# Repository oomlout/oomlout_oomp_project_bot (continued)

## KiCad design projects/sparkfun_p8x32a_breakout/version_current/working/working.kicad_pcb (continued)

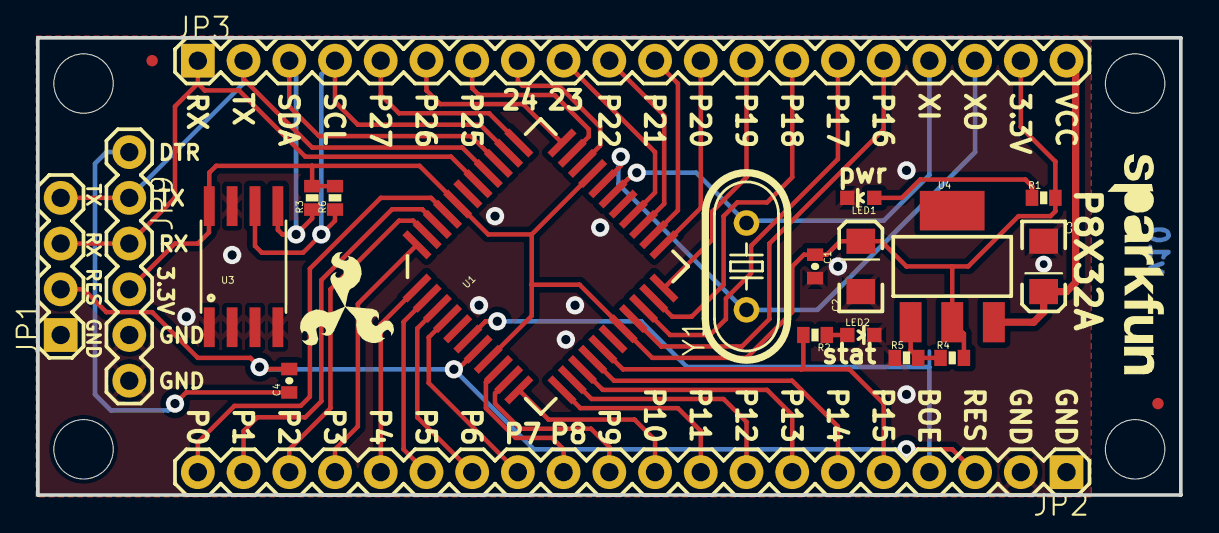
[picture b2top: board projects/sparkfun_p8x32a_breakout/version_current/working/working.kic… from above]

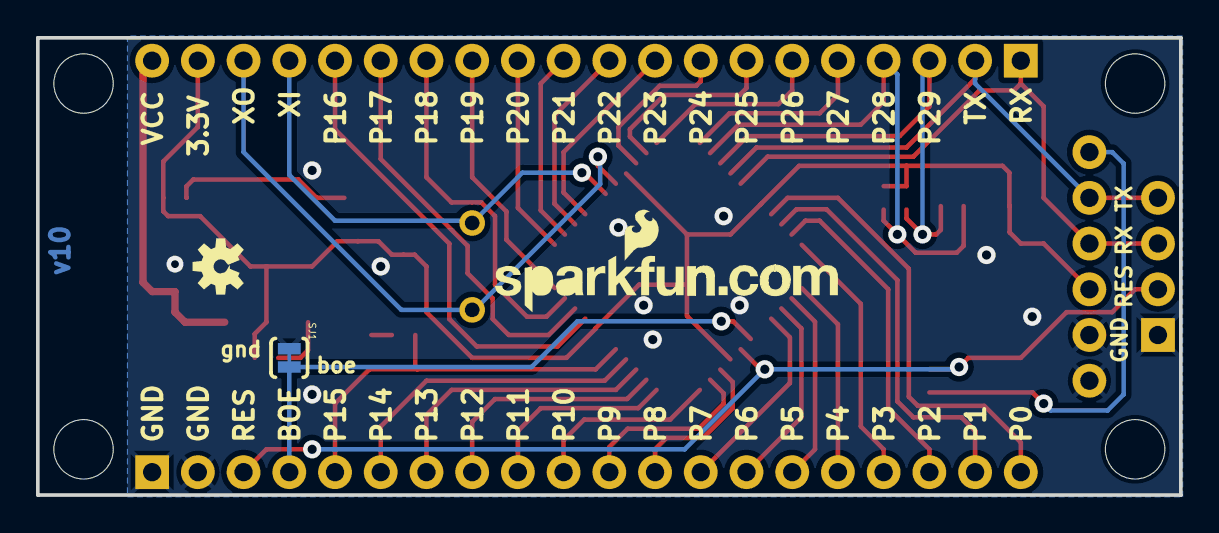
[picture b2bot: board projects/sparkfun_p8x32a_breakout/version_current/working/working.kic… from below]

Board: 2 copper layers, 63.5 x 25.4 mm, 34 parts (3 on the bottom side), 43 nets.

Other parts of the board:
JP6, JP8: LOGO-SFESK; SFE-LOGO-FLAME

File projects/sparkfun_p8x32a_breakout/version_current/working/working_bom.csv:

"Id";"Designator";"Footprint";"Quantity";"Designation";"Supplier and ref";
1;"JP13,JP12,JP10,JP11";"STAND-OFF";4;"STAND-OFF";;;
2;"JP8,JP6,JP7";"SFE-LOGO-FLAME";3;"LOGO-SFESK";;;
3;"JP9";"FTDI_BASIC";1;"FTDI_BASICPTH";;;
4;"JP3,JP2";"1X20";2;"M20";;;
5;"JP1";"1X04";1;"PropPlug";;;
6;"R6,R3";"0402-RES";2;"10k";;;
7;"U3";"SO08-EIAJ";1;"EEPROM-I2CEIAJ";;;
8;"C4,C1";"0402-CAP";2;"0.1uF";;;
9;"JP14";"SFE-NEW-WEB";1;"LOGO-SFENW2";;;
10;"FRAME1";"CREATIVE_COMMONS";1;"FRAME-LETTER";;;
11;"R1,R2";"0402-RES";2;"330";;;
12;"JP4,JP15";"MICRO-FIDUCIAL";2;"FIDUCIALUFIDUCIAL";;;
13;"C2,C3";"EIA3216";2;"10uF";;;
14;"R5";"0402-RES";1;"390";;;
15;"U1";"P8X32A-Q44";1;"";;;
16;"LED1";"LED-0603";1;"red";;;
17;"LED2";"LED-0603";1;"yellow";;;
18;"R4";"0402-RES";1;"240";;;
19;"U4";"SOT223";1;"V_REG_317SMD";;;
20;"Y1";"HC49U-V";1;"";;;
21;"SJ1";"SJ_2S-TRACE";1;"SOLDERJUMPERTRACE";;;
22;"U$1";"OSHW-LOGO-S";1;"OSHW-LOGOS";;;
23;"JP5";"SFE-NEW-WEBLOGO";1;"LOGO-SFENEW";;;

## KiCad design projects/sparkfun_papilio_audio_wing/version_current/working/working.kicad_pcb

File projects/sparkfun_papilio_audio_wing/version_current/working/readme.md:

# Papilio_Audio_Wing by sparkfun  
This is a harvested standardized copy of a project from github.  
The original project can be found at:  
https://github.com/sparkfun/Papilio_Audio_Wing  
Please consult that link for additional, details, files, and license information.  
Note: It was auto harvested and if the original repo had more than one board file or anything out of the ordinary the files here are likely not representative.

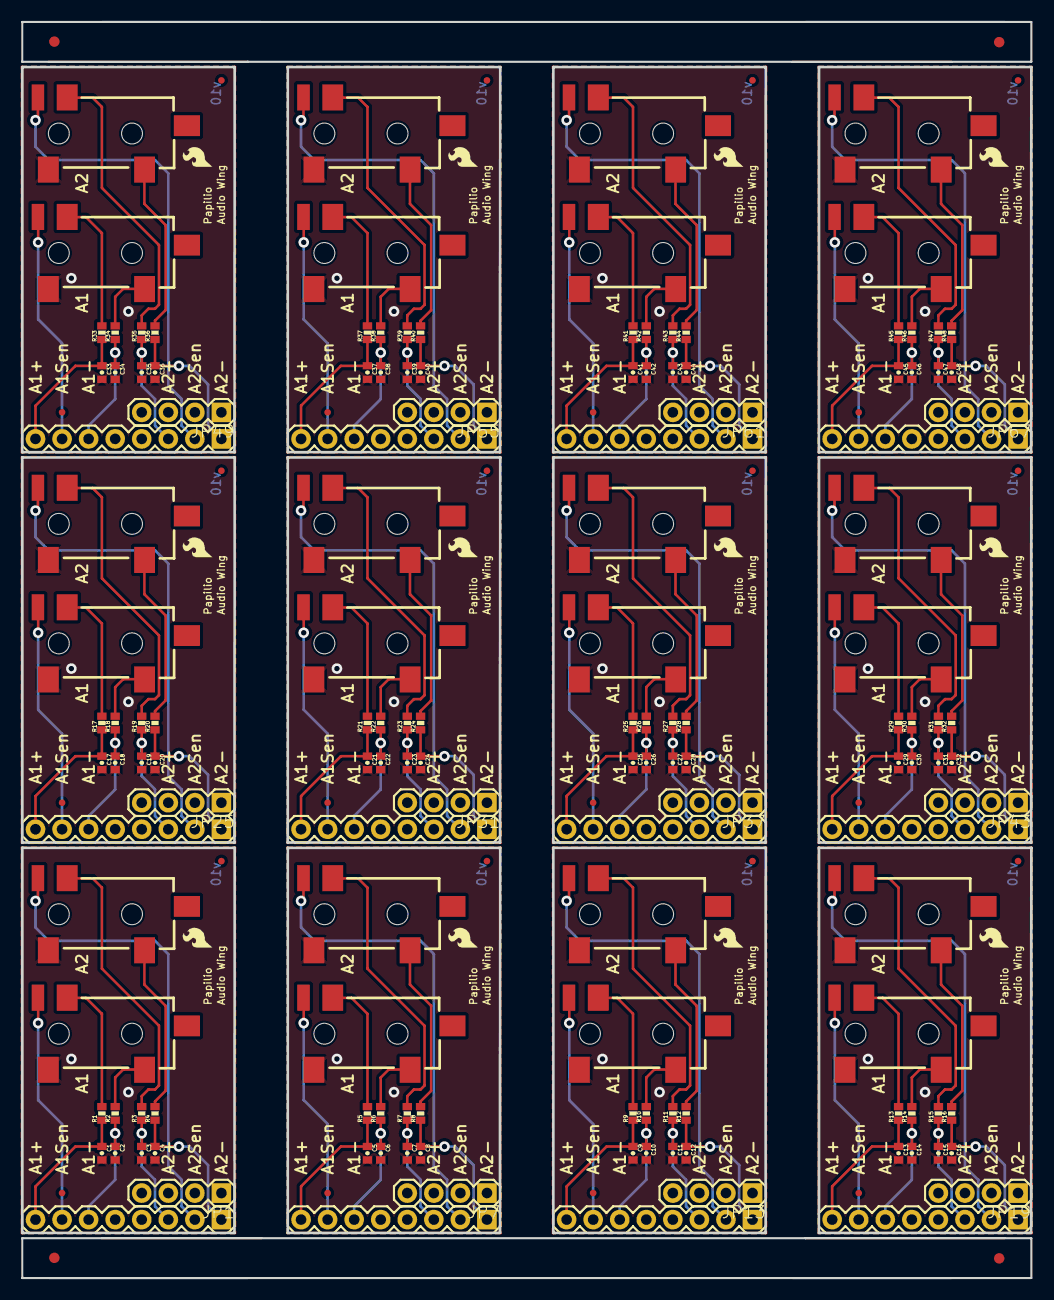
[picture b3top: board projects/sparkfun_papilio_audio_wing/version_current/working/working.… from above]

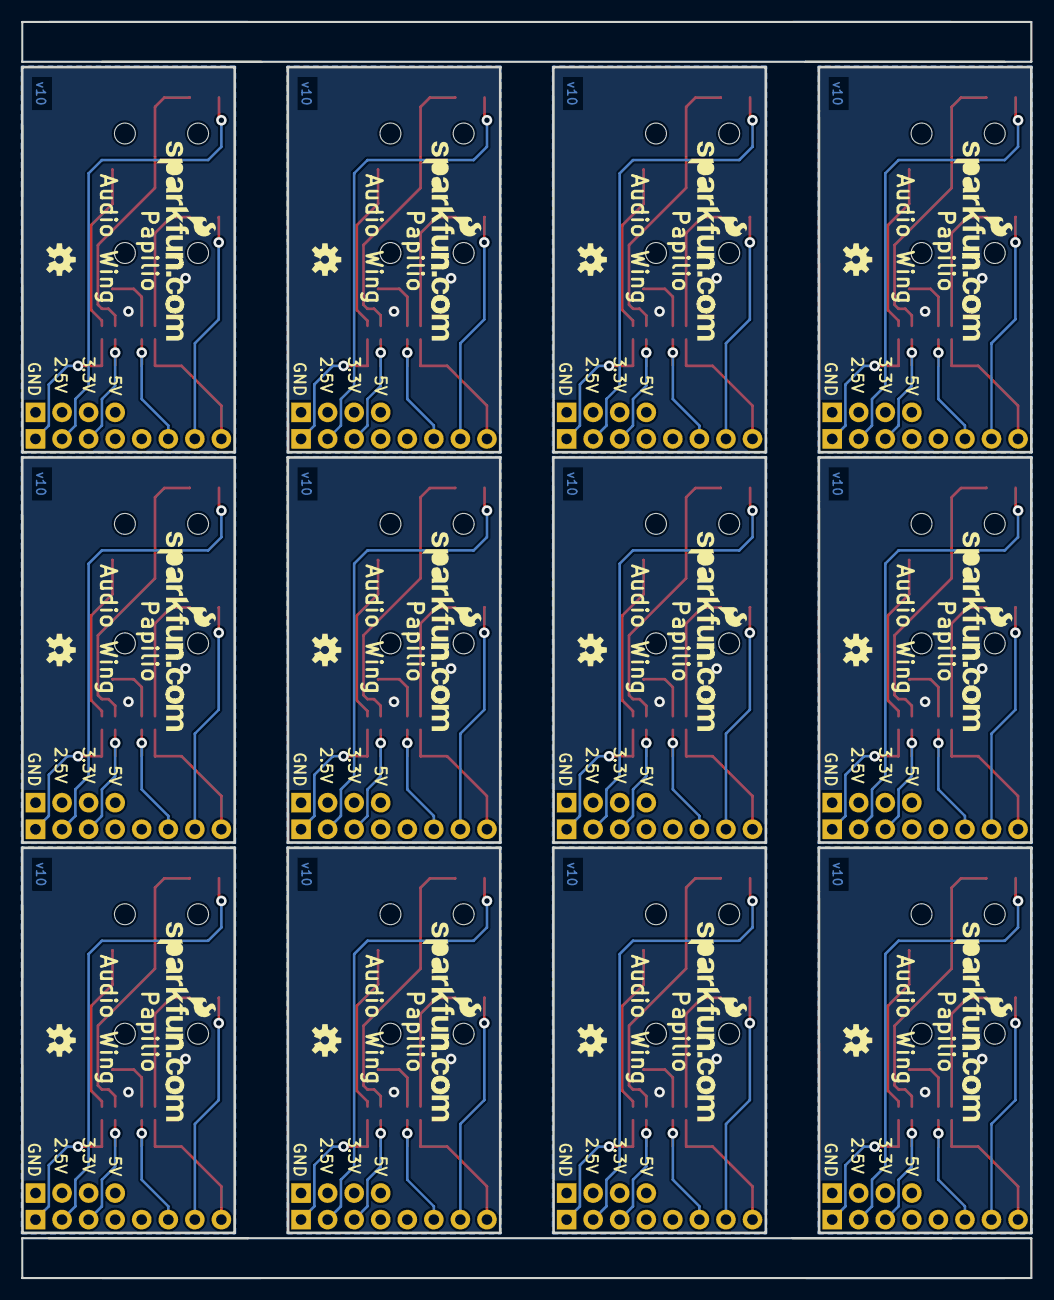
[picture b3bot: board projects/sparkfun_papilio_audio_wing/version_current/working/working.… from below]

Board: 2 copper layers, 96.5 x 120.1 mm, 208 parts (24 on the bottom side), 132 nets.

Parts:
AJ1, AJ2, AJ3, AJ4, AJ5, AJ6, AJ7, AJ8, AJ9, AJ10, AJ11, AJ12, AJ13, AJ14, AJ15, AJ16, AJ17, AJ18, AJ19, AJ20, AJ21, AJ22, AJ23, AJ24: AUDIO-JACK2SMD; AUDIO-JACK-3.5MM-SMD
C1, C2, C3, C4, C5, C6, C7, C8, C9, C10, C11, C12, C13, C14, C15, C16, C17, C18, C19, C20, C21, C22, C23, C24, C25, C26, C27, C28, C29, C30, C31, C32, C33, C34, C35, C36, C37, C38, C39, C40, C41, C42, C43, C44, C45, C46, C47, C48: 4.7nF; 0402-CAP
E$1, E$2, E$3, E$4: FIDUCIAL-1X2
JP1, JP7, JP13, JP19, JP25, JP31, JP37, JP43, JP49, JP55, JP61, JP67: 1X04
JP2, JP8, JP14, JP20, JP26, JP32, JP38, JP44, JP50, JP56, JP62, JP68: 1X08
JP3, JP9, JP15, JP21, JP27, JP33, JP39, JP45, JP51, JP57, JP63, JP69: LOGO-SFESK; SFE-LOGO-FLAME
JP4, JP10, JP16, JP22, JP28, JP34, JP40, JP46, JP52, JP58, JP64, JP70: LOGO-SFENEW; SFE-NEW-WEBLOGO
JP5, JP6, JP11, JP12, JP17, JP18, JP23, JP24, JP29, JP30, JP35, JP36, JP41, JP42, JP47, JP48, JP53, JP54, JP59, JP60, JP65, JP66, JP71, JP72: FIDUCIALUFIDUCIAL; MICRO-FIDUCIAL
R1, R2, R3, R4, R5, R6, R7, R8, R9, R10, R11, R12, R13, R14, R15, R16, R17, R18, R19, R20, R21, R22, R23, R24, R25, R26, R27, R28, R29, R30, R31, R32, R33, R34, R35, R36, R37, R38, R39, R40, R41, R42, R43, R44, R45, R46, R47, R48: 3.3k; 0402-RES
U$1, U$2, U$3, U$4, U$5, U$6, U$7, U$8, U$9, U$10, U$11, U$12: OSHW-LOGOS; OSHW-LOGO-S

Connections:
A1+: C1.1, JP2.8, R1.1
A1+1: C5.1, JP8.8, R5.1
A1+2: C9.1, JP14.8, R9.1
A1+3: C13.1, JP20.8, R13.1
A1+4: C17.1, JP26.8, R17.1
A1+5: C21.1, JP32.8, R21.1
A1+6: C25.1, JP38.8, R25.1
A1+7: C29.1, JP44.8, R29.1
A1+8: C33.1, JP50.8, R33.1
A1+9: C37.1, JP56.8, R37.1
A1+10: C41.1, JP62.8, R41.1
A1+11: C45.1, JP68.8, R45.1
A1-: C2.1, JP2.6, R2.1
A1-1: C6.1, JP8.6, R6.1
A1-2: C10.1, JP14.6, R10.1
A1-3: C14.1, JP20.6, R14.1
A1-4: C18.1, JP26.6, R18.1
A1-5: C22.1, JP32.6, R22.1
A1-6: C26.1, JP38.6, R26.1
A1-7: C30.1, JP44.6, R30.1
A1-8: C34.1, JP50.6, R34.1
A1-9: C38.1, JP56.6, R38.1
A1-10: C42.1, JP62.6, R42.1
A1-11: C46.1, JP68.6, R46.1
A1SEN: AJ1.RSH, JP2.7
A1SEN1: AJ3.RSH, JP8.7
A1SEN2: AJ5.RSH, JP14.7
A1SEN3: AJ7.RSH, JP20.7
A1SEN4: AJ9.RSH, JP26.7
A1SEN5: AJ11.RSH, JP32.7
A1SEN6: AJ13.RSH, JP38.7
A1SEN7: AJ15.RSH, JP44.7
A1SEN8: AJ17.RSH, JP50.7
A1SEN9: AJ19.RSH, JP56.7
A1SEN10: AJ21.RSH, JP62.7
A1SEN11: AJ23.RSH, JP68.7
A2+: C3.1, JP2.3, R3.1
A2+1: C7.1, JP8.3, R7.1
A2+2: C11.1, JP14.3, R11.1
A2+3: C15.1, JP20.3, R15.1
A2+4: C19.1, JP26.3, R19.1
A2+5: C23.1, JP32.3, R23.1
A2+6: C27.1, JP38.3, R27.1
A2+7: C31.1, JP44.3, R31.1
A2+8: C35.1, JP50.3, R35.1
A2+9: C39.1, JP56.3, R39.1
A2+10: C43.1, JP62.3, R43.1
A2+11: C47.1, JP68.3, R47.1
A2-: C4.1, JP2.1, R4.1
A2-1: C8.1, JP8.1, R8.1
A2-2: C12.1, JP14.1, R12.1
A2-3: C16.1, JP20.1, R16.1
A2-4: C20.1, JP26.1, R20.1
A2-5: C24.1, JP32.1, R24.1
A2-6: C28.1, JP38.1, R28.1
A2-7: C32.1, JP44.1, R32.1
A2-8: C36.1, JP50.1, R36.1
A2-9: C40.1, JP56.1, R40.1
A2-10: C44.1, JP62.1, R44.1
A2-11: C48.1, JP68.1, R48.1
A2SEN: AJ2.RSH, JP2.2
A2SEN1: AJ4.RSH, JP8.2
A2SEN2: AJ6.RSH, JP14.2
A2SEN3: AJ8.RSH, JP20.2
A2SEN4: AJ10.RSH, JP26.2
A2SEN5: AJ12.RSH, JP32.2
A2SEN6: AJ14.RSH, JP38.2
A2SEN7: AJ16.RSH, JP44.2
A2SEN8: AJ18.RSH, JP50.2
A2SEN9: AJ20.RSH, JP56.2
A2SEN10: AJ22.RSH, JP62.2
A2SEN11: AJ24.RSH, JP68.2
GND: AJ1.SLEEVE, AJ2.SLEEVE, C1.2, C2.2, C3.2, C4.2, JP1.1
GND1: AJ3.SLEEVE, AJ4.SLEEVE, C5.2, C6.2, C7.2, C8.2, JP7.1
GND2: AJ5.SLEEVE, AJ6.SLEEVE, C9.2, C10.2, C11.2, C12.2, JP13.1
GND3: AJ7.SLEEVE, AJ8.SLEEVE, C13.2, C14.2, C15.2, C16.2, JP19.1
GND4: AJ9.SLEEVE, AJ10.SLEEVE, C17.2, C18.2, C19.2, C20.2, JP25.1
GND5: AJ11.SLEEVE, AJ12.SLEEVE, C21.2, C22.2, C23.2, C24.2, JP31.1
GND6: AJ13.SLEEVE, AJ14.SLEEVE, C25.2, C26.2, C27.2, C28.2, JP37.1
GND7: AJ15.SLEEVE, AJ16.SLEEVE, C29.2, C30.2, C31.2, C32.2, JP43.1
GND8: AJ17.SLEEVE, AJ18.SLEEVE, C33.2, C34.2, C35.2, C36.2, JP49.1
GND9: AJ19.SLEEVE, AJ20.SLEEVE, C37.2, C38.2, C39.2, C40.2, JP55.1
GND10: AJ21.SLEEVE, AJ22.SLEEVE, C41.2, C42.2, C43.2, C44.2, JP61.1
GND11: AJ23.SLEEVE, AJ24.SLEEVE, C45.2, C46.2, C47.2, C48.2, JP67.1
unnamed: AJ2.RING, R3.2
unnamed: AJ2.TIP, R4.2
unnamed: AJ1.RING, R1.2
unnamed: AJ1.TIP, R2.2
unnamed: AJ4.RING, R7.2
unnamed: AJ4.TIP, R8.2
unnamed: AJ3.RING, R5.2
unnamed: AJ3.TIP, R6.2
unnamed: AJ6.RING, R11.2
unnamed: AJ6.TIP, R12.2
unnamed: AJ5.RING, R9.2
unnamed: AJ5.TIP, R10.2
unnamed: AJ8.RING, R15.2
unnamed: AJ8.TIP, R16.2
unnamed: AJ7.RING, R13.2
unnamed: AJ7.TIP, R14.2
unnamed: AJ10.RING, R19.2
unnamed: AJ10.TIP, R20.2
unnamed: AJ9.RING, R17.2
unnamed: AJ9.TIP, R18.2
unnamed: AJ12.RING, R23.2
unnamed: AJ12.TIP, R24.2
unnamed: AJ11.RING, R21.2
unnamed: AJ11.TIP, R22.2
unnamed: AJ14.RING, R27.2
unnamed: AJ14.TIP, R28.2
unnamed: AJ13.RING, R25.2
unnamed: AJ13.TIP, R26.2
unnamed: AJ16.RING, R31.2
unnamed: AJ16.TIP, R32.2
unnamed: AJ15.RING, R29.2
unnamed: AJ15.TIP, R30.2
unnamed: AJ18.RING, R35.2
unnamed: AJ18.TIP, R36.2
unnamed: AJ17.RING, R33.2
unnamed: AJ17.TIP, R34.2
unnamed: AJ20.RING, R39.2
unnamed: AJ20.TIP, R40.2
unnamed: AJ19.RING, R37.2
unnamed: AJ19.TIP, R38.2
unnamed: AJ22.RING, R43.2
unnamed: AJ22.TIP, R44.2
unnamed: AJ21.RING, R41.2
unnamed: AJ21.TIP, R42.2
unnamed: AJ24.RING, R47.2
unnamed: AJ24.TIP, R48.2
unnamed: AJ23.RING, R45.2
unnamed: AJ23.TIP, R46.2

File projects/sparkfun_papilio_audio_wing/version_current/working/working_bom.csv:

"Id";"Designator";"Footprint";"Quantity";"Designation";"Supplier and ref";
1;"R17,R29,R43,R15,R1,R6,R44,R14,R48,R34,R23,R4,R16,R42,R19,R31,R24,R7,R40,R36,R28,R9,R2,R5,R41,R18,R13,R27,R3,R21,R33,R25,R10,R46,R39,R45,R47,R32,R11,R20,R26,R8,R35,R22,R30,R38,R12,R37";"0402-RES";48;"3.3k";;;
2;"JP66,JP24,JP11,JP54,JP53,JP6,JP12,JP65,JP23,JP71,JP18,JP59,JP17,JP72,JP5,JP47,JP42,JP29,JP36,JP60,JP35,JP48,JP30,JP41";"MICRO-FIDUCIAL";24;"FIDUCIALUFIDUCIAL";;;
3;"C33,C38,C29,C48,C1,C32,C2,C35,C15,C47,C5,C42,C30,C12,C18,C25,C3,C20,C41,C44,C6,C22,C31,C19,C13,C24,C23,C43,C11,C37,C17,C46,C7,C26,C34,C39,C40,C45,C4,C14,C9,C16,C10,C28,C8,C27,C36,C21";"0402-CAP";48;"4.7nF";;;
4;"JP13,JP25,JP55,JP19,JP31,JP7,JP49,JP37,JP43,JP61,JP67,JP1";"1X04";12;"";;;
5;"JP32,JP8,JP68,JP56,JP44,JP50,JP14,JP38,JP62,JP26,JP20,JP2";"1X08";12;"";;;
6;"JP63,JP3,JP69,JP33,JP9,JP45,JP39,JP21,JP57,JP51,JP27,JP15";"SFE-LOGO-FLAME";12;"LOGO-SFESK";;;
7;"AJ15,AJ12,AJ16,AJ20,AJ5,AJ6,AJ22,AJ18,AJ13,AJ24,AJ14,AJ8,AJ10,AJ17,AJ2,AJ11,AJ1,AJ4,AJ9,AJ3,AJ19,AJ23,AJ7,AJ21";"AUDIO-JACK-3.5MM-SMD";24;"AUDIO-JACK2SMD";;;
8;"E$2,E$1,E$4,E$3";"FIDUCIAL-1X2";4;"";;;
9;"U$7,U$4,U$8,U$9,U$1,U$5,U$10,U$3,U$2,U$12,U$6,U$11";"OSHW-LOGO-S";12;"OSHW-LOGOS";;;
10;"JP34,JP40,JP16,JP28,JP64,JP22,JP4,JP10,JP46,JP70,JP52,JP58";"SFE-NEW-WEBLOGO";12;"LOGO-SFENEW";;;

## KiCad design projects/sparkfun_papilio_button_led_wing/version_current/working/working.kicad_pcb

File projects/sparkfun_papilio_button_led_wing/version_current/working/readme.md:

# Papilio_Button_LED_Wing by sparkfun  
This is a harvested standardized copy of a project from github.  
The original project can be found at:  
https://github.com/sparkfun/Papilio_Button_LED_Wing  
Please consult that link for additional, details, files, and license information.  
Note: It was auto harvested and if the original repo had more than one board file or anything out of the ordinary the files here are likely not representative.

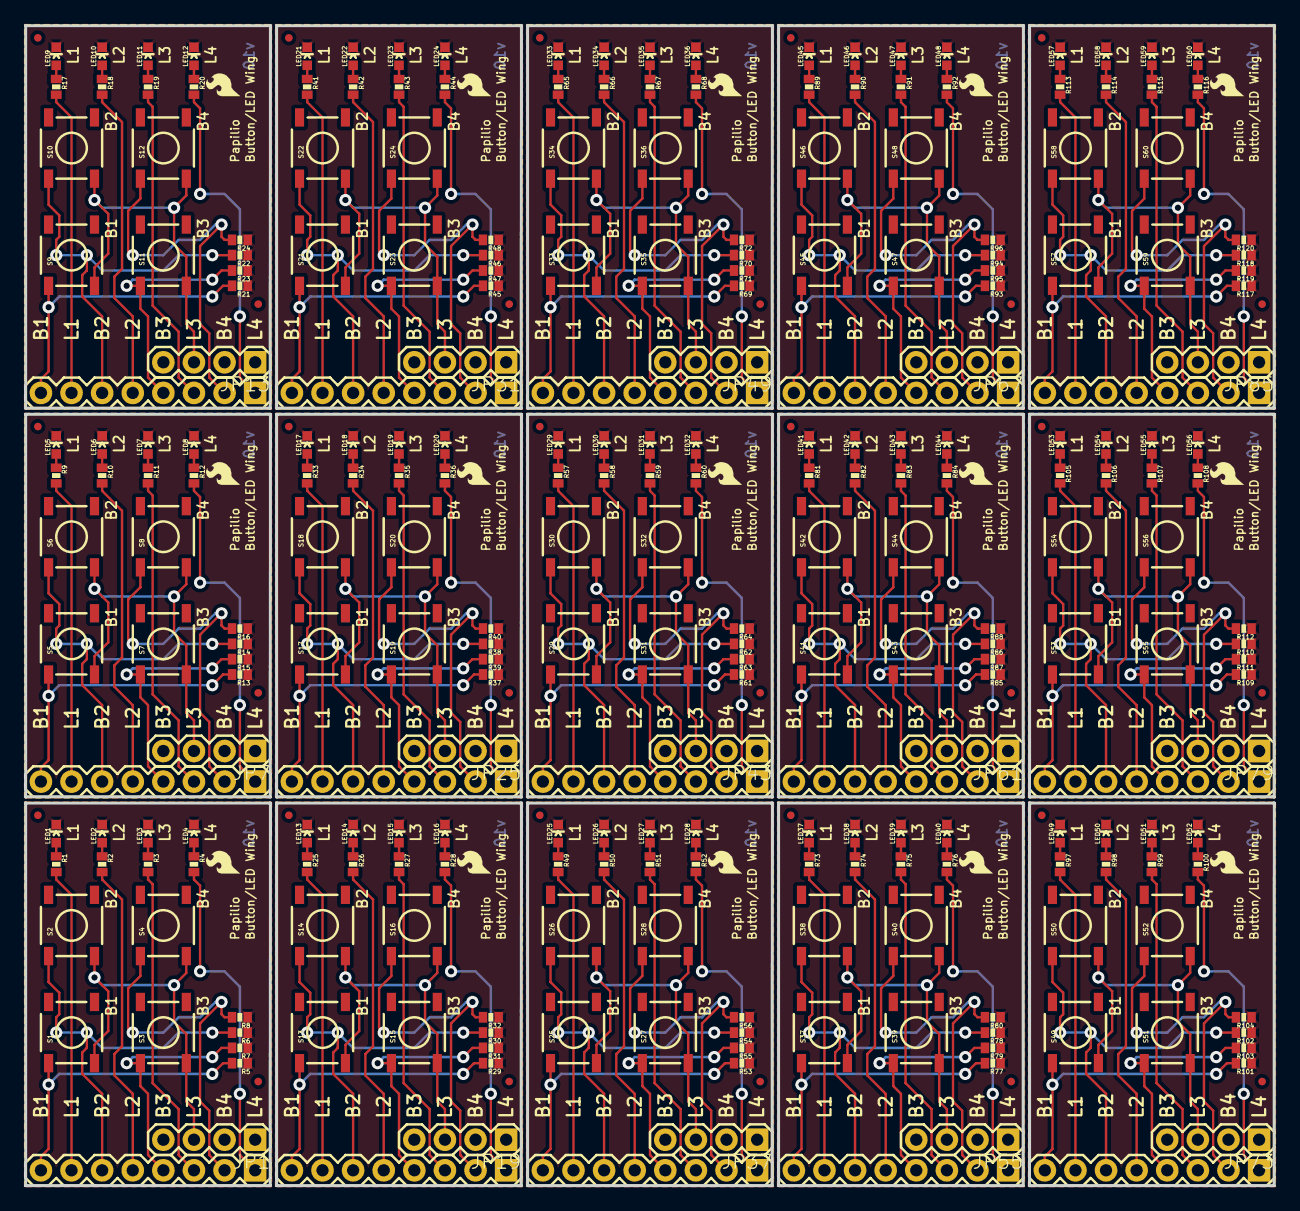
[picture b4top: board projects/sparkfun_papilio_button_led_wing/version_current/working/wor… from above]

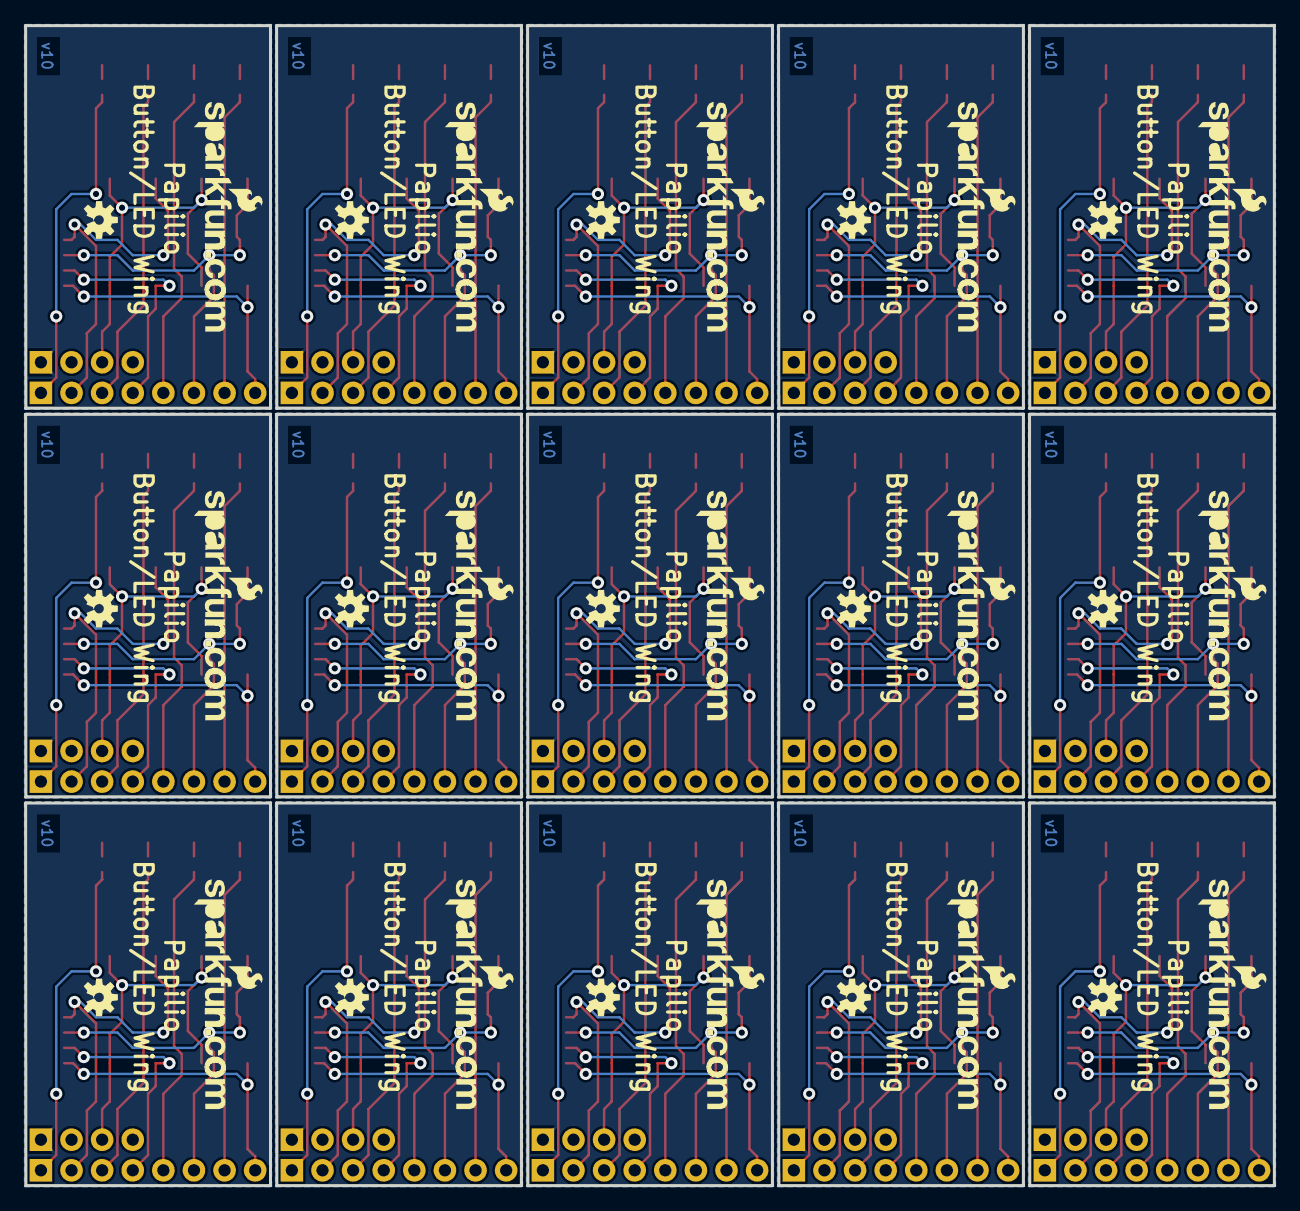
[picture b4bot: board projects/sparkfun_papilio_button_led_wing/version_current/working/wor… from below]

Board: 2 copper layers, 103.6 x 96.3 mm, 345 parts (30 on the bottom side), 210 nets.

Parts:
JP1, JP7, JP13, JP19, JP25, JP31, JP37, JP43, JP49, JP55, JP61, JP67, JP73, JP79, JP85: 1X04
JP2, JP8, JP14, JP20, JP26, JP32, JP38, JP44, JP50, JP56, JP62, JP68, JP74, JP80, JP86: 1X08
JP3, JP9, JP15, JP21, JP27, JP33, JP39, JP45, JP51, JP57, JP63, JP69, JP75, JP81, JP87: LOGO-SFESK; SFE-LOGO-FLAME
JP4, JP10, JP16, JP22, JP28, JP34, JP40, JP46, JP52, JP58, JP64, JP70, JP76, JP82, JP88: LOGO-SFENEW; SFE-NEW-WEBLOGO
JP5, JP6, JP11, JP12, JP17, JP18, JP23, JP24, JP29, JP30, JP35, JP36, JP41, JP42, JP47, JP48, JP53, JP54, JP59, JP60, JP65, JP66, JP71, JP72, JP77, JP78, JP83, JP84, JP89, JP90: FIDUCIALUFIDUCIAL; MICRO-FIDUCIAL
LED1, LED5, LED9, LED13, LED17, LED21, LED25, LED29, LED33, LED37, LED41, LED45, LED49, LED53, LED57: Red; LED-0603
LED2, LED6, LED10, LED14, LED18, LED22, LED26, LED30, LED34, LED38, LED42, LED46, LED50, LED54, LED58: Yellow; LED-0603
LED3, LED7, LED11, LED15, LED19, LED23, LED27, LED31, LED35, LED39, LED43, LED47, LED51, LED55, LED59: Green; LED-0603
LED4, LED8, LED12, LED16, LED20, LED24, LED28, LED32, LED36, LED40, LED44, LED48, LED52, LED56, LED60: Blue; LED-0603
R1, R2, R3, R4, R9, R10, R11, R12, R17, R18, R19, R20, R25, R26, R27, R28, R33, R34, R35, R36, R41, R42, R43, R44, R49, R50, R51, R52, R57, R58, R59, R60, R65, R66, R67, R68, R73, R74, R75, R76, R81, R82, R83, R84, R89, R90, R91, R92, R97, R98, R99, R100, R105, R106, R107, R108, R113, R114, R115, R116: 220; 0402-RES
R5, R6, R7, R8, R13, R14, R15, R16, R21, R22, R23, R24, R29, R30, R31, R32, R37, R38, R39, R40, R45, R46, R47, R48, R53, R54, R55, R56, R61, R62, R63, R64, R69, R70, R71, R72, R77, R78, R79, R80, R85, R86, R87, R88, R93, R94, R95, R96, R101, R102, R103, R104, R109, R110, R111, R112, R117, R118, R119, R120: 10k; 0402-RES
S1, S5, S9, S13, S17, S21, S25, S29, S33, S37, S41, S45, S49, S53, S57: Button 1; TACTILE_SWITCH_SMD
S2, S6, S10, S14, S18, S22, S26, S30, S34, S38, S42, S46, S50, S54, S58: Button 2; TACTILE_SWITCH_SMD
S3, S7, S11, S15, S19, S23, S27, S31, S35, S39, S43, S47, S51, S55, S59: Button 3; TACTILE_SWITCH_SMD
S4, S8, S12, S16, S20, S24, S28, S32, S36, S40, S44, S48, S52, S56, S60: Button 4; TACTILE_SWITCH_SMD
U$1, U$2, U$3, U$4, U$5, U$6, U$7, U$8, U$9, U$10, U$11, U$12, U$13, U$14, U$15: OSHW-LOGOS; OSHW-LOGO-S

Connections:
3.3V: JP1.3, S1.3, S2.3, S3.3, S4.3
3.3V1: JP7.3, S5.3, S6.3, S7.3, S8.3
3.3V2: JP13.3, S9.3, S10.3, S11.3, S12.3
3.3V3: JP19.3, S13.3, S14.3, S15.3, S16.3
3.3V4: JP25.3, S17.3, S18.3, S19.3, S20.3
3.3V5: JP31.3, S21.3, S22.3, S23.3, S24.3
3.3V6: JP37.3, S25.3, S26.3, S27.3, S28.3
3.3V7: JP43.3, S29.3, S30.3, S31.3, S32.3
3.3V8: JP49.3, S33.3, S34.3, S35.3, S36.3
3.3V9: JP55.3, S37.3, S38.3, S39.3, S40.3
3.3V10: JP61.3, S41.3, S42.3, S43.3, S44.3
3.3V11: JP67.3, S45.3, S46.3, S47.3, S48.3
3.3V12: JP73.3, S49.3, S50.3, S51.3, S52.3
3.3V13: JP79.3, S53.3, S54.3, S55.3, S56.3
3.3V14: JP85.3, S57.3, S58.3, S59.3, S60.3
GND: JP1.1, LED1.C, LED2.C, LED3.C, LED4.C, R5.1, R6.1, R7.1, R8.1
GND1: JP7.1, LED5.C, LED6.C, LED7.C, LED8.C, R13.1, R14.1, R15.1, R16.1
GND2: JP13.1, LED9.C, LED10.C, LED11.C, LED12.C, R21.1, R22.1, R23.1, R24.1
GND3: JP19.1, LED13.C, LED14.C, LED15.C, LED16.C, R29.1, R30.1, R31.1, R32.1
GND4: JP25.1, LED17.C, LED18.C, LED19.C, LED20.C, R37.1, R38.1, R39.1, R40.1
GND5: JP31.1, LED21.C, LED22.C, LED23.C, LED24.C, R45.1, R46.1, R47.1, R48.1
GND6: JP37.1, LED25.C, LED26.C, LED27.C, LED28.C, R53.1, R54.1, R55.1, R56.1
GND7: JP43.1, LED29.C, LED30.C, LED31.C, LED32.C, R61.1, R62.1, R63.1, R64.1
GND8: JP49.1, LED33.C, LED34.C, LED35.C, LED36.C, R69.1, R70.1, R71.1, R72.1
GND9: JP55.1, LED37.C, LED38.C, LED39.C, LED40.C, R77.1, R78.1, R79.1, R80.1
GND10: JP61.1, LED41.C, LED42.C, LED43.C, LED44.C, R85.1, R86.1, R87.1, R88.1
GND11: JP67.1, LED45.C, LED46.C, LED47.C, LED48.C, R93.1, R94.1, R95.1, R96.1
GND12: JP73.1, LED49.C, LED50.C, LED51.C, LED52.C, R101.1, R102.1, R103.1, R104.1
GND13: JP79.1, LED53.C, LED54.C, LED55.C, LED56.C, R109.1, R110.1, R111.1, R112.1
GND14: JP85.1, LED57.C, LED58.C, LED59.C, LED60.C, R117.1, R118.1, R119.1, R120.1
LED1: JP2.7, R1.2
LED2: JP2.5, R2.2
LED3: JP2.3, R3.2
LED4: JP2.1, R4.2
LED5: JP8.7, R9.2
LED6: JP8.5, R10.2
LED7: JP8.3, R11.2
LED8: JP8.1, R12.2
LED9: JP14.7, R17.2
LED10: JP14.5, R18.2
LED11: JP14.3, R19.2
LED12: JP14.1, R20.2
LED13: JP20.7, R25.2
LED14: JP20.5, R26.2
LED15: JP20.3, R27.2
LED16: JP20.1, R28.2
LED17: JP26.7, R33.2
LED18: JP26.5, R34.2
LED19: JP26.3, R35.2
LED20: JP26.1, R36.2
LED21: JP32.7, R41.2
LED22: JP32.5, R42.2
LED23: JP32.3, R43.2
LED24: JP32.1, R44.2
LED25: JP38.7, R49.2
LED26: JP38.5, R50.2
LED27: JP38.3, R51.2
LED28: JP38.1, R52.2
LED29: JP44.7, R57.2
LED30: JP44.5, R58.2
LED31: JP44.3, R59.2
LED32: JP44.1, R60.2
LED33: JP50.7, R65.2
LED34: JP50.5, R66.2
LED35: JP50.3, R67.2
LED36: JP50.1, R68.2
LED37: JP56.7, R73.2
LED38: JP56.5, R74.2
LED39: JP56.3, R75.2
LED40: JP56.1, R76.2
LED41: JP62.7, R81.2
LED42: JP62.5, R82.2
LED43: JP62.3, R83.2
LED44: JP62.1, R84.2
LED45: JP68.7, R89.2
LED46: JP68.5, R90.2
LED47: JP68.3, R91.2
LED48: JP68.1, R92.2
LED49: JP74.7, R97.2
LED50: JP74.5, R98.2
LED51: JP74.3, R99.2
LED52: JP74.1, R100.2
LED53: JP80.7, R105.2
LED54: JP80.5, R106.2
LED55: JP80.3, R107.2
LED56: JP80.1, R108.2
LED57: JP86.7, R113.2
LED58: JP86.5, R114.2
LED59: JP86.3, R115.2
LED60: JP86.1, R116.2
unnamed: LED1.A, R1.1
unnamed: LED5.A, R9.1
unnamed: LED7.A, R11.1
unnamed: LED3.A, R3.1
unnamed: LED2.A, R2.1
unnamed: LED4.A, R4.1
unnamed: LED6.A, R10.1
unnamed: LED8.A, R12.1
unnamed: LED9.A, R17.1
unnamed: LED11.A, R19.1
unnamed: LED10.A, R18.1
unnamed: LED12.A, R20.1
unnamed: LED13.A, R25.1
unnamed: LED15.A, R27.1
unnamed: LED14.A, R26.1
unnamed: LED16.A, R28.1
unnamed: LED17.A, R33.1
unnamed: LED19.A, R35.1
unnamed: LED18.A, R34.1
unnamed: LED20.A, R36.1
unnamed: LED21.A, R41.1
unnamed: LED23.A, R43.1
unnamed: LED22.A, R42.1
unnamed: LED24.A, R44.1
unnamed: LED25.A, R49.1
unnamed: LED27.A, R51.1
unnamed: LED26.A, R50.1
unnamed: LED28.A, R52.1
unnamed: LED29.A, R57.1
unnamed: LED31.A, R59.1
unnamed: LED30.A, R58.1
unnamed: LED32.A, R60.1
unnamed: LED33.A, R65.1
unnamed: LED35.A, R67.1
unnamed: LED34.A, R66.1
unnamed: LED36.A, R68.1
unnamed: LED37.A, R73.1
unnamed: LED39.A, R75.1
unnamed: LED38.A, R74.1
unnamed: LED40.A, R76.1
unnamed: LED41.A, R81.1
unnamed: LED43.A, R83.1
unnamed: LED42.A, R82.1
unnamed: LED44.A, R84.1
unnamed: LED45.A, R89.1
unnamed: LED47.A, R91.1
unnamed: LED46.A, R90.1
unnamed: LED48.A, R92.1
unnamed: LED49.A, R97.1
unnamed: LED51.A, R99.1
unnamed: LED50.A, R98.1
unnamed: LED52.A, R100.1
unnamed: LED53.A, R105.1
unnamed: LED55.A, R107.1
unnamed: LED54.A, R106.1
unnamed: LED56.A, R108.1
unnamed: LED57.A, R113.1
unnamed: LED59.A, R115.1
unnamed: LED58.A, R114.1
unnamed: LED60.A, R116.1
PB1: JP2.8, R5.2, S1.1
PB2: JP2.6, R6.2, S2.1
PB3: JP2.4, R7.2, S3.1
PB4: JP2.2, R8.2, S4.1
PB5: JP8.8, R13.2, S5.1
PB6: JP8.6, R14.2, S6.1
PB7: JP8.4, R15.2, S7.1
PB8: JP8.2, R16.2, S8.1
PB9: JP14.8, R21.2, S9.1
PB10: JP14.6, R22.2, S10.1
PB11: JP14.4, R23.2, S11.1
PB12: JP14.2, R24.2, S12.1
PB13: JP20.8, R29.2, S13.1
PB14: JP20.6, R30.2, S14.1
PB15: JP20.4, R31.2, S15.1
PB16: JP20.2, R32.2, S16.1
PB17: JP26.8, R37.2, S17.1
PB18: JP26.6, R38.2, S18.1
PB19: JP26.4, R39.2, S19.1
PB20: JP26.2, R40.2, S20.1
PB21: JP32.8, R45.2, S21.1
PB22: JP32.6, R46.2, S22.1
PB23: JP32.4, R47.2, S23.1
PB24: JP32.2, R48.2, S24.1
PB25: JP38.8, R53.2, S25.1
PB26: JP38.6, R54.2, S26.1
PB27: JP38.4, R55.2, S27.1
PB28: JP38.2, R56.2, S28.1
PB29: JP44.8, R61.2, S29.1
PB30: JP44.6, R62.2, S30.1
PB31: JP44.4, R63.2, S31.1
PB32: JP44.2, R64.2, S32.1
PB33: JP50.8, R69.2, S33.1
PB34: JP50.6, R70.2, S34.1
PB35: JP50.4, R71.2, S35.1
PB36: JP50.2, R72.2, S36.1
PB37: JP56.8, R77.2, S37.1
PB38: JP56.6, R78.2, S38.1
PB39: JP56.4, R79.2, S39.1
PB40: JP56.2, R80.2, S40.1
PB41: JP62.8, R85.2, S41.1
PB42: JP62.6, R86.2, S42.1
PB43: JP62.4, R87.2, S43.1
PB44: JP62.2, R88.2, S44.1
PB45: JP68.8, R93.2, S45.1
PB46: JP68.6, R94.2, S46.1
PB47: JP68.4, R95.2, S47.1
PB48: JP68.2, R96.2, S48.1
PB49: JP74.8, R101.2, S49.1
PB50: JP74.6, R102.2, S50.1
PB51: JP74.4, R103.2, S51.1
PB52: JP74.2, R104.2, S52.1
PB53: JP80.8, R109.2, S53.1
PB54: JP80.6, R110.2, S54.1
PB55: JP80.4, R111.2, S55.1
PB56: JP80.2, R112.2, S56.1
PB57: JP86.8, R117.2, S57.1
PB58: JP86.6, R118.2, S58.1
PB59: JP86.4, R119.2, S59.1
PB60: JP86.2, R120.2, S60.1

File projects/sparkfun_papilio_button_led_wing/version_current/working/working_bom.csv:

"Id";"Designator";"Footprint";"Quantity";"Designation";"Supplier and ref";
1;"S2,S30,S38,S58,S10,S14,S34,S6,S42,S50,S18,S22,S54,S26,S46";"TACTILE_SWITCH_SMD";15;"Button 2";;;
2;"R59,R2,R12,R76,R41,R36,R116,R28,R114,R99,R34,R73,R19,R97,R50,R106,R81,R74,R67,R9,R3,R51,R83,R44,R91,R92,R1,R89,R108,R25,R35,R115,R107,R90,R11,R33,R43,R100,R20,R75,R84,R57,R60,R52,R4,R68,R17,R26,R10,R18,R58,R113,R49,R98,R66,R82,R27,R65,R42,R105";"0402-RES";60;"220";;;
3;"R32,R78,R39,R29,R62,R38,R21,R53,R8,R101,R31,R37,R47,R61,R7,R6,R5,R103,R63,R104,R119,R87,R117,R16,R79,R102,R40,R110,R45,R109,R120,R70,R96,R13,R30,R24,R54,R77,R93,R72,R80,R69,R85,R56,R111,R86,R22,R14,R15,R112,R118,R94,R23,R71,R46,R48,R64,R95,R88,R55";"0402-RES";60;"10k";;;
4;"LED20,LED44,LED36,LED8,LED12,LED60,LED48,LED4,LED32,LED16,LED40,LED56,LED28,LED24,LED52";"LED-0603";15;"Blue";;;
5;"JP12,JP42,JP78,JP90,JP36,JP41,JP59,JP48,JP17,JP65,JP47,JP11,JP23,JP83,JP53,JP89,JP84,JP5,JP66,JP35,JP24,JP71,JP29,JP18,JP60,JP6,JP77,JP72,JP30,JP54";"MICRO-FIDUCIAL";30;"FIDUCIALUFIDUCIAL";;;
6;"LED39,LED7,LED51,LED43,LED3,LED27,LED47,LED11,LED23,LED59,LED35,LED31,LED19,LED15,LED55";"LED-0603";15;"Green";;;
7;"JP50,JP8,JP14,JP26,JP62,JP80,JP44,JP86,JP68,JP38,JP32,JP74,JP20,JP2,JP56";"1X08";15;"";;;
8;"S7,S3,S59,S55,S11,S39,S31,S43,S15,S27,S47,S23,S51,S35,S19";"TACTILE_SWITCH_SMD";15;"Button 3";;;
9;"S12,S56,S36,S4,S16,S44,S32,S60,S28,S52,S24,S40,S8,S20,S48";"TACTILE_SWITCH_SMD";15;"Button 4";;;
10;"LED14,LED54,LED38,LED30,LED50,LED42,LED18,LED58,LED2,LED26,LED46,LED34,LED22,LED6,LED10";"LED-0603";15;"Yellow";;;
11;"JP9,JP27,JP69,JP81,JP45,JP63,JP33,JP21,JP51,JP75,JP87,JP15,JP39,JP57,JP3";"SFE-LOGO-FLAME";15;"LOGO-SFESK";;;
12;"S13,S57,S9,S1,S21,S41,S17,S29,S33,S37,S25,S45,S53,S5,S49";"TACTILE_SWITCH_SMD";15;"Button 1";;;
13;"LED45,LED49,LED21,LED25,LED9,LED5,LED53,LED1,LED33,LED37,LED13,LED29,LED41,LED17,LED57";"LED-0603";15;"Red";;;
14;"JP73,JP25,JP31,JP55,JP79,JP85,JP37,JP7,JP61,JP43,JP49,JP13,JP67,JP1,JP19";"1X04";15;"";;;
15;"JP88,JP28,JP52,JP16,JP82,JP64,JP4,JP58,JP70,JP22,JP10,JP76,JP46,JP40,JP34";"SFE-NEW-WEBLOGO";15;"LOGO-SFENEW";;;
16;"U$1,U$12,U$5,U$2,U$11,U$14,U$4,U$6,U$7,U$3,U$15,U$13,U$8,U$10,U$9";"OSHW-LOGO-S";15;"OSHW-LOGOS";;;

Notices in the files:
projects/sparkfun_opto_isolator_breakout/version_current/working/working.kicad_sch:
Released under the Creative Commons
projects/sparkfun_p8x32a_breakout/version_current/working/working.kicad_sch:
http://creativecommons.org/licenses/by-sa/3.0
parts and their libraries:
Released under the Creative Commons Attribution Share-Alike 3.0 License
Released under the Creative Commons Attribution Share-Alike 4.0 License
